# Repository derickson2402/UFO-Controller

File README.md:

# UFO-Controller

This summer, several of us wanted to build some quadcopter drones (what can I say, we're a house full of bored engineers :smiley:).
Eventually, we'd like to hook up FPV cameras, GPS units, and some other fun gizmos so that we can do cool stuff like FPV racing, autonomous path following with GPS, and smart object detection and wayfinding using computer vision.
Currently the project is in early stages, but I am documenting all the software as I go and when we have everything working I will make sure to include assembly instructions as well.

Much of the transmitter code is extended from [akarsh98](https://github.com/akarsh98) on GitHub and [this guide on PPM via Arduino](https://quadmeup.com/generate-ppm-signal-with-arduino/). Thanks akarsh and Pawel!

## Included Files

Some of the code used here is from projects from almost a decade ago, so I made sure to grab a copy of all the libraries and such that are used here.
Each folder contains some component of either testing/building the drone, and each comes with its own README and any dependencies.

Folder | Description
---|---|
```Arduino-ISP```     | Copied from Arduino IDE built-in example 11. Allows an Uno to program a Nano over ISP
```Wiring-Diagrams``` | PCB designs and board pinouts for transceiver, flight controller, etc for KiCad 6.0. Includes KiCad files for MPU breakout board.
```Hardware-Tests```  | Various programs for verifying that individual electronic components are working
```MultiWii```        | Flight control software from [MultiWii.com](http://www.multiwii.com/)
```MultiWii-GUI```    | Configuration GUI for ```MultiWii```
```Transceiver```     | Instructions for using pair of Arduino as radio transmitter to drone

## Testing/Verifying Hardware

In the ```Hardware-Tests``` folder are some basic programs for testing that various components are working.
There is another README in the folder which will walk you through everything.
I highly recommend you verify all of your hardware is working correctly BEFORE trying everything together, since there is nothing worse than spending hours on a "software" bug that doesn't actually exist.
Plus if you're like me you bought the cheapest stuff you could find and there's a good chance it won't all work right :smiley:.

## Configuring VS Code IDE

If you are like me, you really hate the default Arduino IDE and you would rather use VS Code.
To do this:

1. Install the Arduino VS Code extension
2. Choose AVR programmer and Arduino Nano board
3. In ```c_cpp_properties.json```, update ```compilerPath```, ```includePath```, and ```forcedInclude``` so your machine's section matches that of the Arduino (basically tell intellisense to use the Arduino's compiler)
4. Add ```USBCON``` to ```defines``` in ```c_cpp_properties.json```
5. If you need 3rd-party libraries, put them in ```src``` in the root of this repo and symlink ```src``` in your code root folder to it (Arduino compiler should recognize the ```src``` folder automatically)

## Resources

- https://create.arduino.cc/projecthub/akarsh98/diy-arduino-based-quadcopter-drone-948153
- https://www.hackster.io/robocircuits/arduino-quadcopter-e618c6
- https://howtomechatronics.com/projects/diy-arduino-rc-transmitter/
- https://www.modelflight.com.au/blog/a-guide-to-understanding-lipo-batteries
- https://www.instructables.com/DJi-F450-Quadcopter-How-to-Build-Home-Built/
- http://www.rctutor.org/the-parts-list.html
- [Read-only Amazon link for parts](https://www.amazon.com/hz/wishlist/ls/1BKLT1DHMK0VX?ref_=wl_share)
- [PPM communication via Arduino](https://quadmeup.com/generate-ppm-signal-with-arduino/)

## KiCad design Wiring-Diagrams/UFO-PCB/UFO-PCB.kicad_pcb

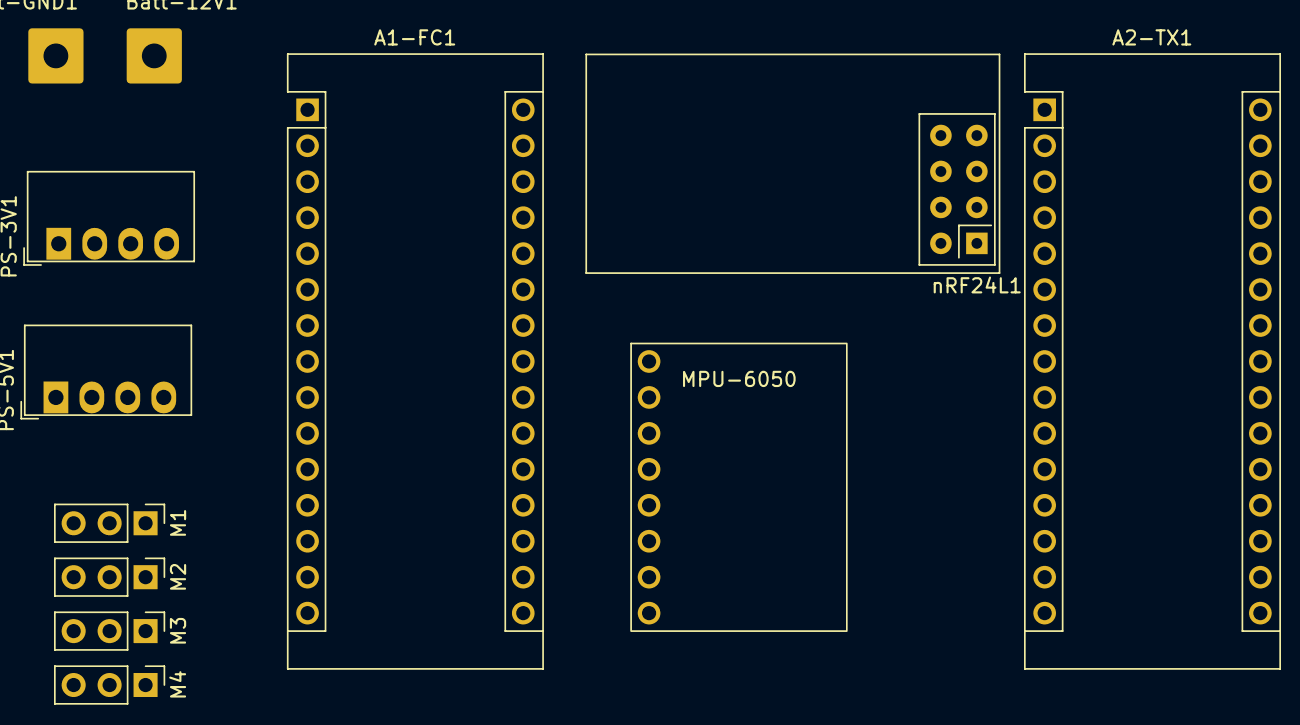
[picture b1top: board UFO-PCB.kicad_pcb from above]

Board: 2 copper layers, 12 parts (0 on the bottom side), 16 nets, no tracks yet.

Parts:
A1-FC1, A2-TX1: Arduino_Nano_v3.x; Arduino_Nano
Batt-12V1: Conn_01x01_Male; SolderWire-1sqmm_1x01_D1.4mm_OD3.9mm
Batt-GND1: Conn_01x01_Male; SolderWire-1sqmm_1x01_D1.4mm_OD3.9mm
M1, M2, M3, M4: Motor_Servo; PinHeader_1x03_P2.54mm_Vertical
MPU-6050: MPU-6050-Breakout
PS-3V1, PS-5V1: MEE1S0305SC; Converter_DCDC_Murata_MEE1SxxxxSC_THT
nRF24L1: NRF24L01_Breakout; nRF24L01_Breakout

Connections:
+BATT: Batt-12V1.1, PS-3V1.2 (+Vin), PS-5V1.2 (+Vin)
GND: Batt-GND1.1, PS-3V1.1 (-Vin), PS-5V1.1 (-Vin)
unnamed: A1-FC1.4 (GND), A1-FC1.30 (VIN), A2-TX1.4 (GND), A2-TX1.30 (VIN), M1.2 (+), M1.3 (-), M2.2 (+), M2.3 (-), M3.2 (+), M3.3 (-), M4.2 (+), M4.3 (-), MPU-6050.1 (VCC), MPU-6050.2 (GND), PS-3V1.3 (-Vout), PS-5V1.3 (-Vout), PS-5V1.4 (+Vout), nRF24L1.1 (GND)
unnamed: A1-FC1.5 (D2), A2-TX1.6 (D3)
unnamed: A1-FC1.9 (D6), M1.1 (PWM)
unnamed: A1-FC1.10 (D7), M2.1 (PWM)
unnamed: A1-FC1.11 (D8), M3.1 (PWM)
unnamed: A1-FC1.12 (D9), M4.1 (PWM)
unnamed: A1-FC1.23 (A4), MPU-6050.4 (SDA)
unnamed: A1-FC1.24 (A5), MPU-6050.3 (SCL)
unnamed: A2-TX1.12 (D9), nRF24L1.4 (~CSN)
unnamed: A2-TX1.13 (D10), nRF24L1.3 (CE)
unnamed: A2-TX1.14 (D11), nRF24L1.6 (MOSI)
unnamed: A2-TX1.15 (D12), nRF24L1.7 (MISO)
unnamed: A2-TX1.16 (D13), nRF24L1.5 (SCK)
unnamed: PS-3V1.4 (+Vout), nRF24L1.2 (VCC)

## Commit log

2022-04-13 Start README
2022-04-24 Add copies of board pinouts, add README docs
2022-04-24 Add IDE setup instructions, add 3rd party libraries
2022-04-24 Add MultiWii files
2022-04-27 Add MultiWii conf, add Transmitter/Receiver, update documentation
2022-04-27 Add MultiWii GUI code and docs
2022-04-27 Add pinout diagrams, start main pcb design
2022-04-28 Update Controller PCB with all components, no traces yet
2022-05-05 Add MPU-6050 symbol diagram, update documentation for transceiver
2022-05-07 Rewrite Transceiver code from scratch, update docs accordingly
2022-05-20 Speed up data packet transfer, resolve #3
2022-07-17 Start adding motion controls to transmitter
2022-07-20 Add motor and ESC hardware testing
    Added simple Arduino sketch to test and calibrate the Electronic Speed Controllers and the motors.
    Includes a Processing sketch with a simple slider for adjusting the speed of the controllers.
2022-07-20 Fix bugs in Motors tests, remove Processing GUI
2022-07-20 Update Motors test with better docs and wiring diagram
2022-07-21 Simplify Motor hardware tests, update docs
    This closes Test motors and ESC's #7
2022-07-21 Rename Diagrams folder
2022-07-21 Fix source files and Sketch structure
2022-07-22 Create Joystick interface, fix Transceiver RX/TX macros
2022-07-22 Add transceiver tests and diagrams
    See #2
2022-07-24 Clarify instructions for Arduino ISP
2022-07-30 Tidy up debug mode in Transceiver code, document bug in #12
